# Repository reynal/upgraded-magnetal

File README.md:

# upgraded-magnetal
Add more controls, baby, add more controls (a MIDI/OSC controller with every control you can think of)

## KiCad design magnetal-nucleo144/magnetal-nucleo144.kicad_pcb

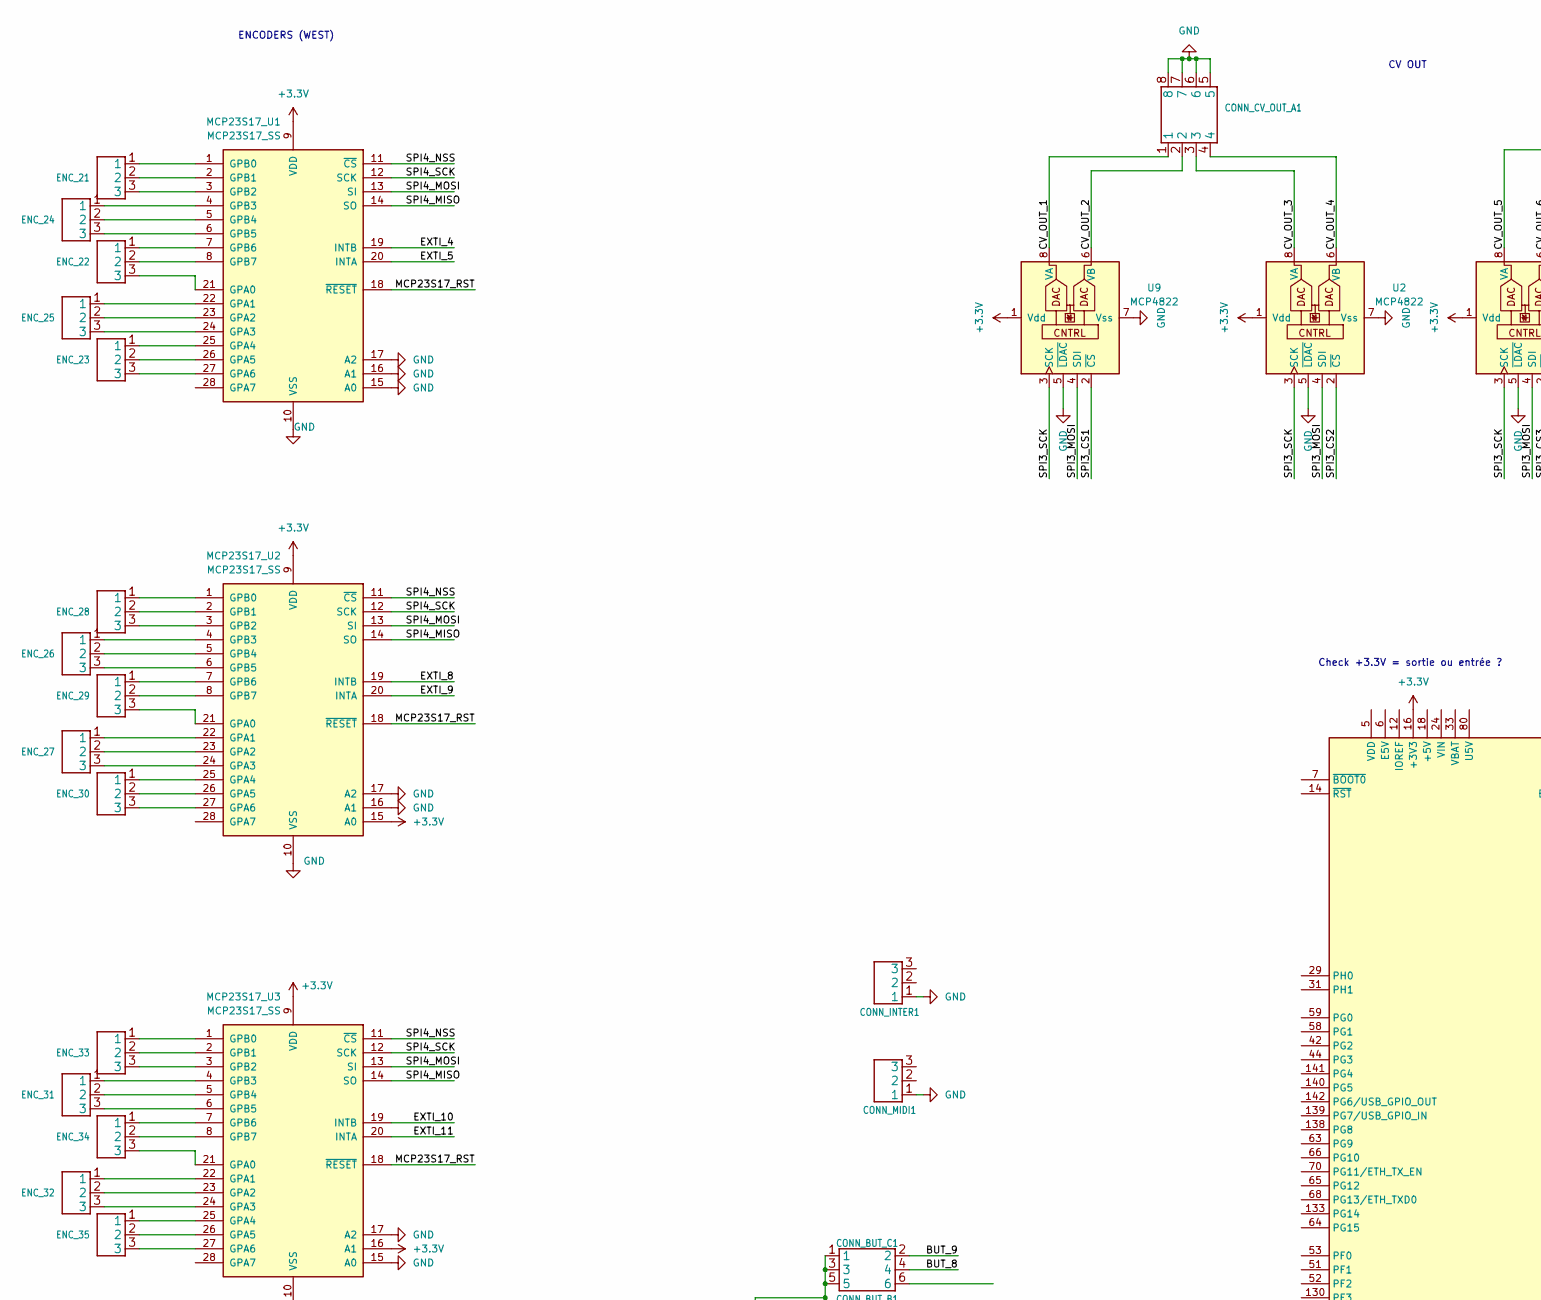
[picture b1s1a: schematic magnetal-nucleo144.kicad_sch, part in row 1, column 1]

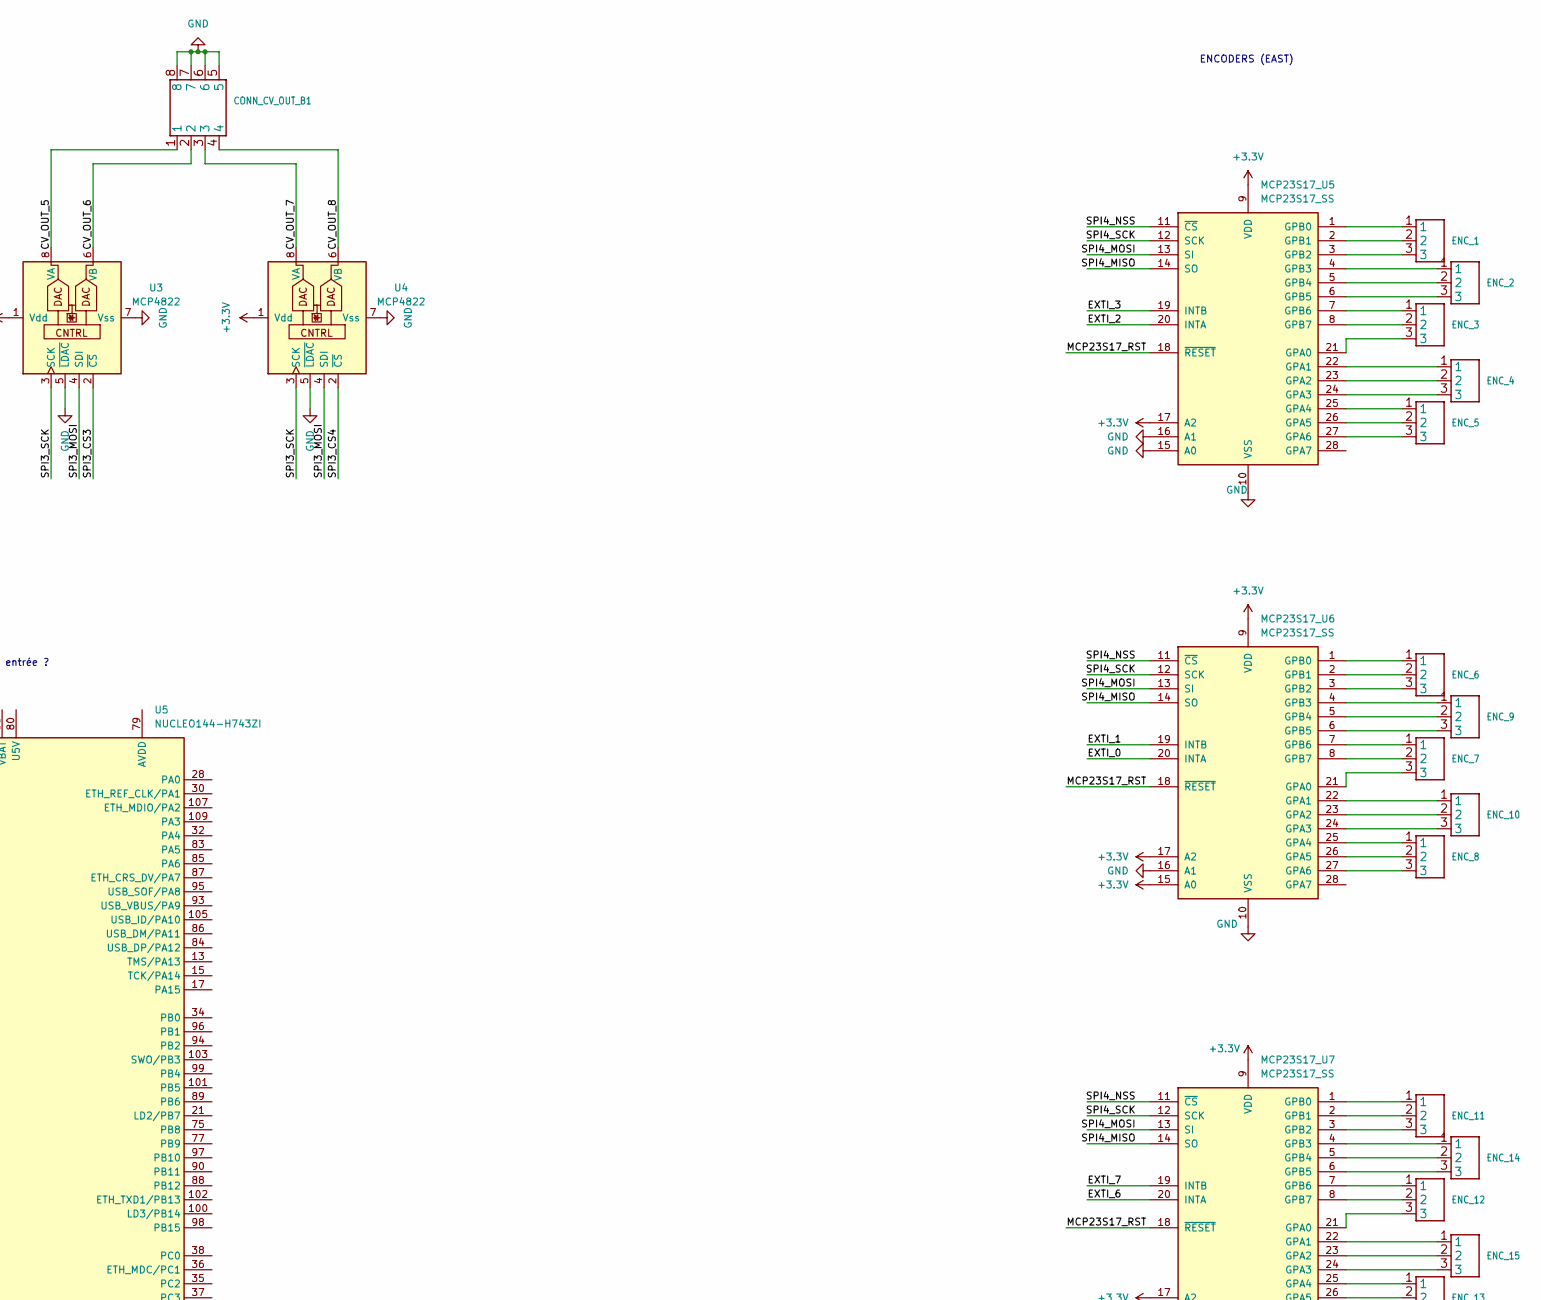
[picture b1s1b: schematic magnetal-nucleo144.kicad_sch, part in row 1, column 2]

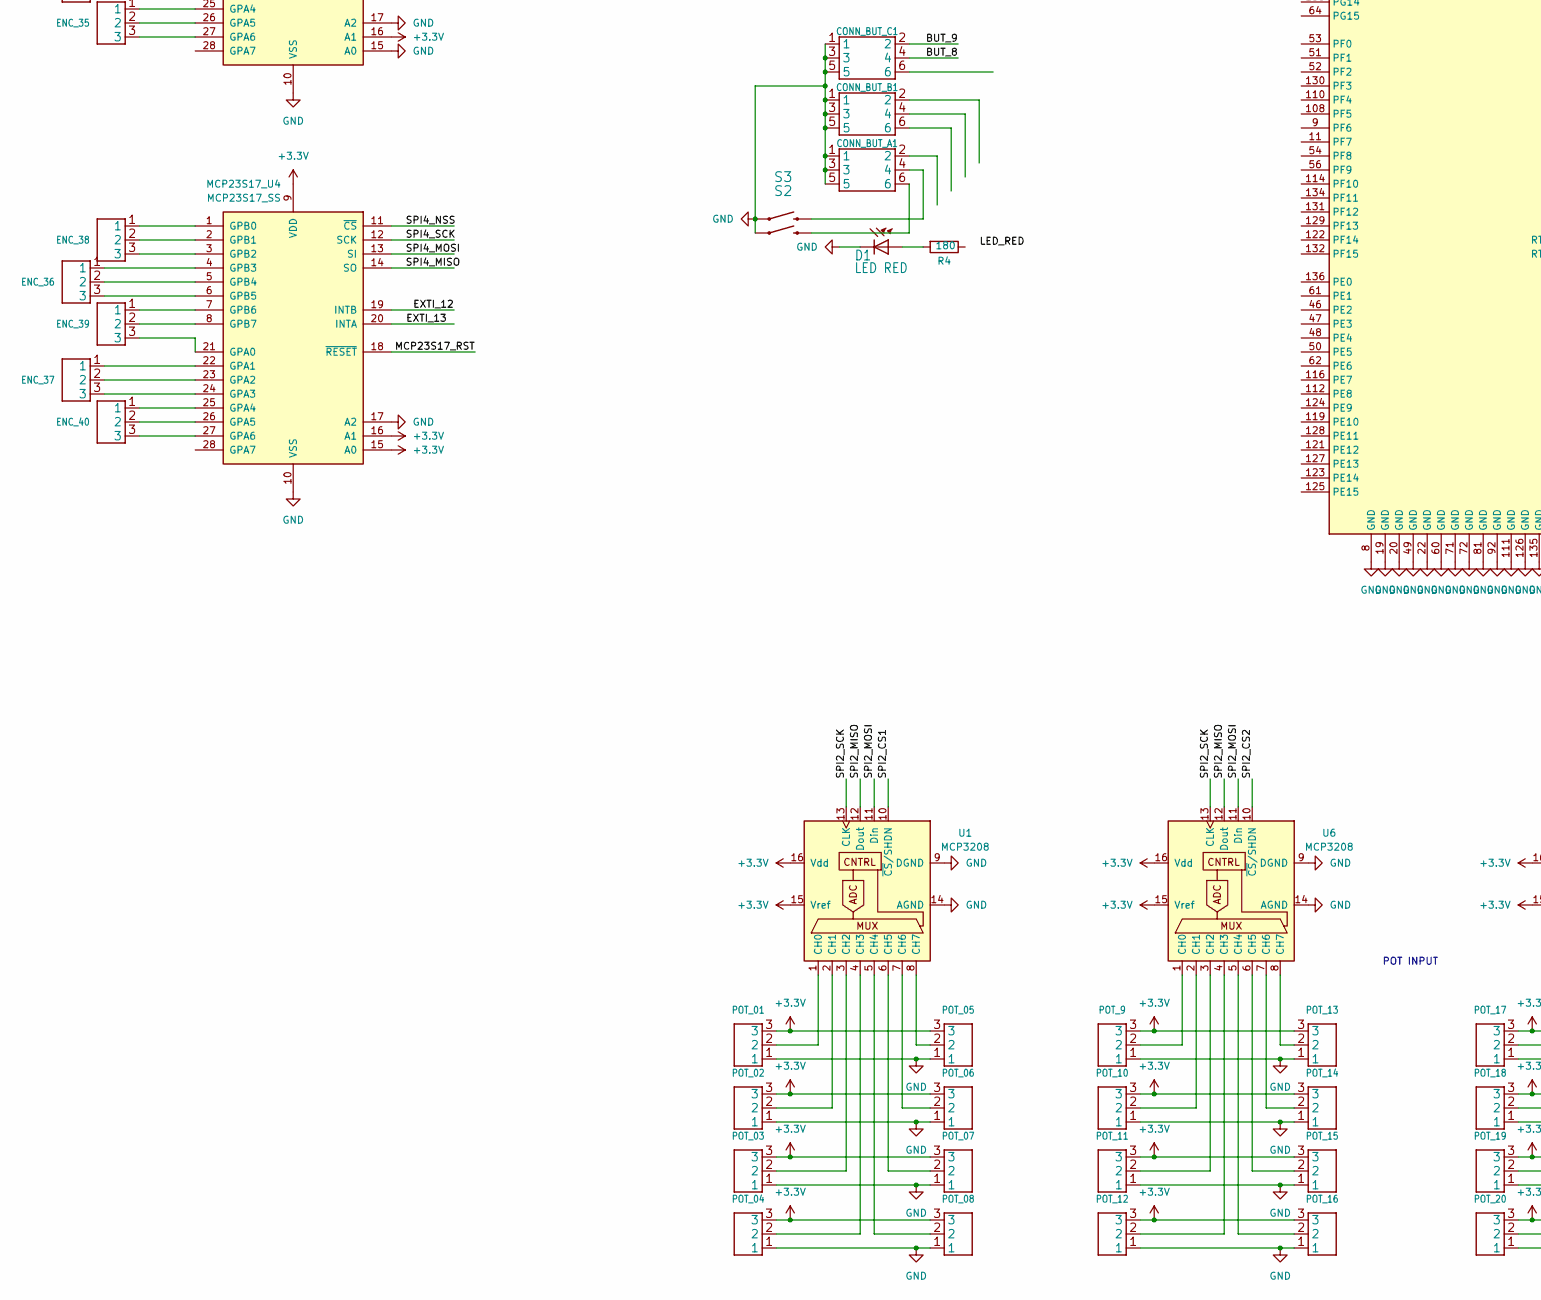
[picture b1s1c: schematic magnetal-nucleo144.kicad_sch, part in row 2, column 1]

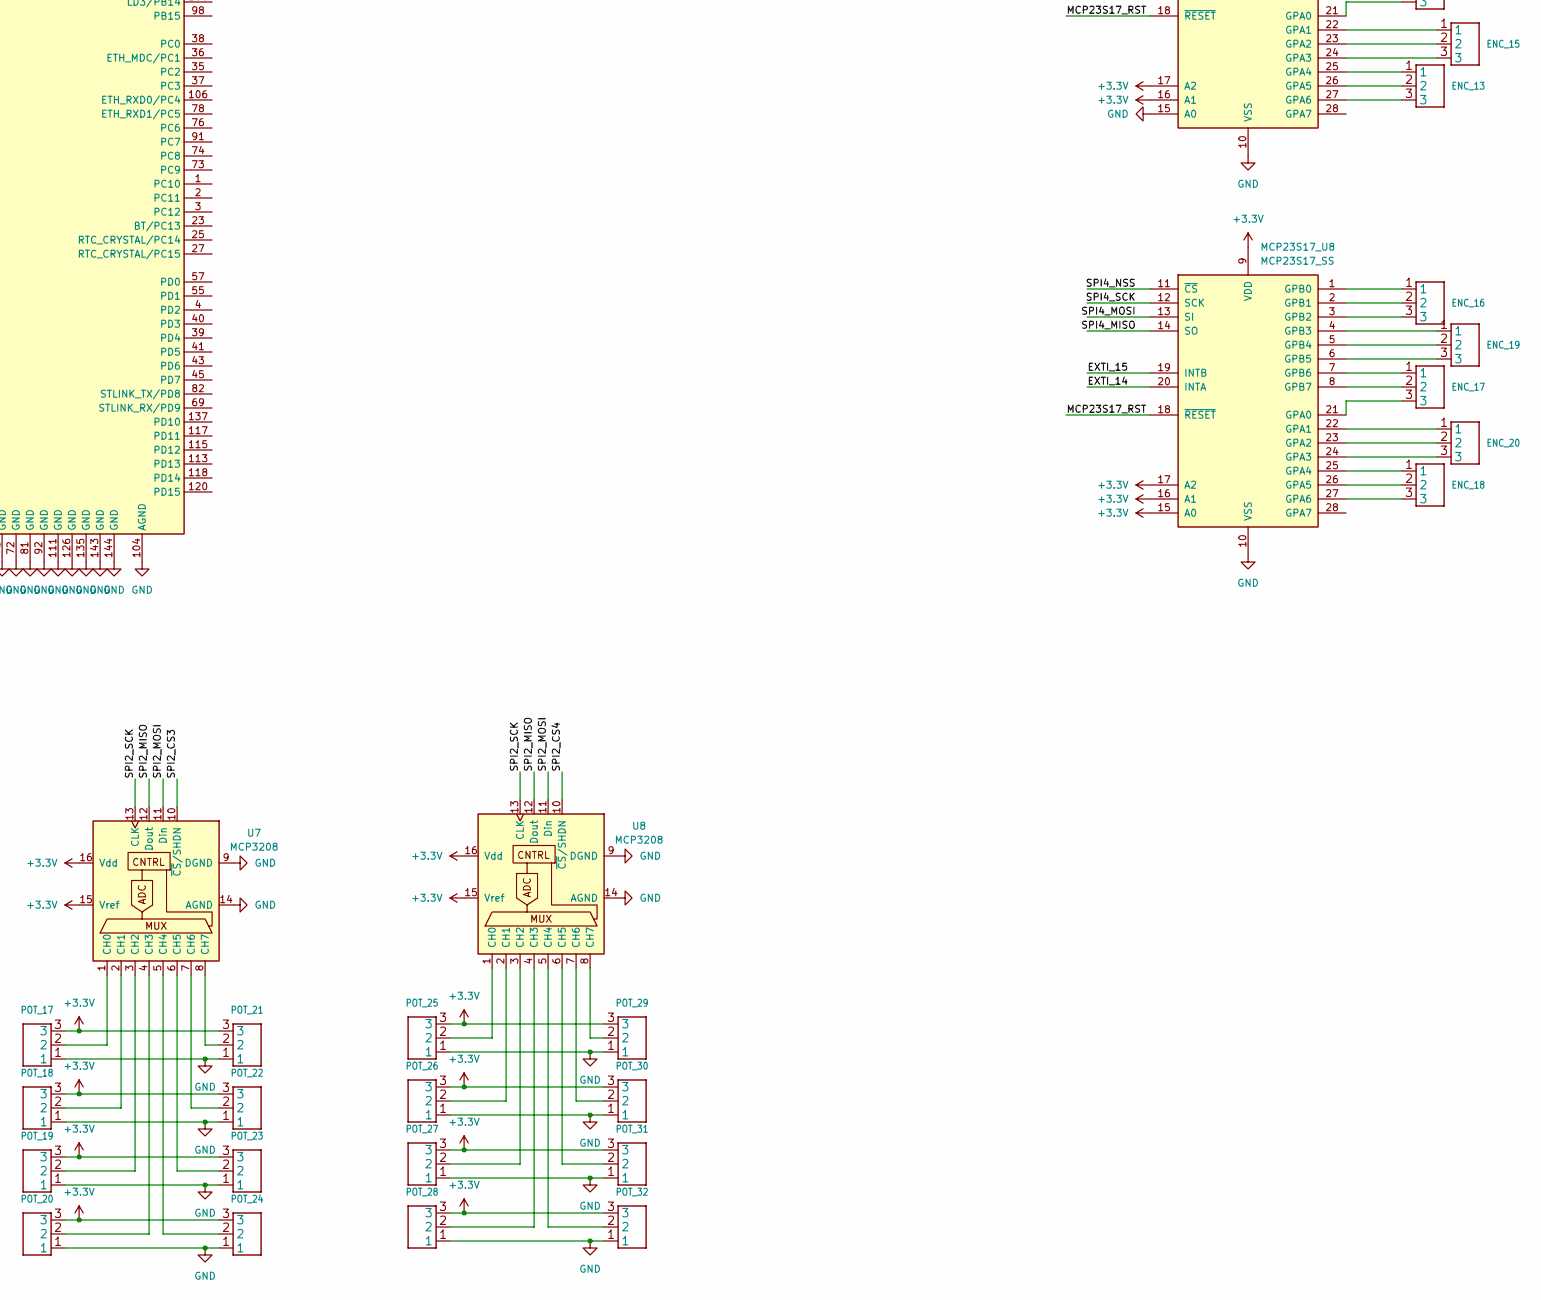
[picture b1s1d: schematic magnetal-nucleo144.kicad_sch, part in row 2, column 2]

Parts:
CONN_BUT_A1: M03X2
CONN_BUT_B1: M03X2
CONN_BUT_C1: M03X2
CONN_CV_OUT_A1: M04X2-FLOW_CONTROLER
CONN_CV_OUT_B1: M04X2-FLOW_CONTROLER
CONN_INTER1: M03
CONN_MIDI1: M03
D1: LED RED; 0805-LED
ENC_1, ENC_2, ENC_3, ENC_4, ENC_5, ENC_6, ENC_7, ENC_8, ENC_9, ENC_10, ENC_11, ENC_12, ENC_13, ENC_14, ENC_15, ENC_16, ENC_17, ENC_18, ENC_19, ENC_20, ENC_21, ENC_22, ENC_23, ENC_24, ENC_25, ENC_26, ENC_27, ENC_28, ENC_29, ENC_30, ENC_31, ENC_32, ENC_33, ENC_34, ENC_35, ENC_36, ENC_37, ENC_38, ENC_39, ENC_40: M03
MCP23S17_U1, MCP23S17_U2, MCP23S17_U3, MCP23S17_U4, MCP23S17_U5, MCP23S17_U6, MCP23S17_U7, MCP23S17_U8: MCP23S17_SS; SSOP-28_5.3x10.2mm_P0.65mm
POT_01, POT_02, POT_03, POT_04, POT_05, POT_06, POT_07, POT_08, POT_9, POT_10, POT_11, POT_12, POT_13, POT_14, POT_15, POT_16, POT_17, POT_18, POT_19, POT_20, POT_21, POT_22, POT_23, POT_24, POT_25, POT_26, POT_27, POT_28, POT_29, POT_30, POT_31, POT_32: M03
R4: 180; R_0805_2012Metric_Pad1.20x1.40mm_HandSolder
S2, S3: TACTILE_SWITCH_PTH_6.0MM_KIT
U1, U6, U7, U8: MCP3208; SOIC-16_3.9x9.9mm_P1.27mm
U2, U3, U4, U9: MCP4822; MSOP-8_3x3mm_P0.65mm
U5: NUCLEO144-H743ZI; ST_Morpho_Connector_144_STLink

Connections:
+3.3V: MCP23S17_U1.9 (VDD), MCP23S17_U2.9 (VDD), MCP23S17_U2.15 (A0), MCP23S17_U3.9 (VDD), MCP23S17_U3.16 (A1), MCP23S17_U4.9 (VDD), MCP23S17_U4.15 (A0), MCP23S17_U4.16 (A1), MCP23S17_U5.9 (VDD), MCP23S17_U5.17 (A2), MCP23S17_U6.9 (VDD), MCP23S17_U6.15 (A0), MCP23S17_U6.17 (A2), MCP23S17_U7.9 (VDD), MCP23S17_U7.16 (A1), MCP23S17_U7.17 (A2), MCP23S17_U8.9 (VDD), MCP23S17_U8.15 (A0), MCP23S17_U8.16 (A1), MCP23S17_U8.17 (A2), POT_01.3, POT_02.3, POT_03.3, POT_04.3, POT_05.3, POT_06.3, POT_07.3, POT_08.3, POT_9.3, POT_10.3, POT_11.3, POT_12.3, POT_13.3, POT_14.3, POT_15.3, POT_16.3, POT_17.3, POT_18.3, POT_19.3, POT_20.3, POT_21.3, POT_22.3, POT_23.3, POT_24.3, POT_25.3, POT_26.3, POT_27.3, POT_28.3, POT_29.3, POT_30.3, POT_31.3, POT_32.3, U1.15 (Vref), U1.16 (Vdd), U2.1 (Vdd), U3.1 (Vdd), U4.1 (Vdd), U5.16 (+3V3), U6.15 (Vref), U6.16 (Vdd), U7.15 (Vref), U7.16 (Vdd), U8.15 (Vref), U8.16 (Vdd), U9.1 (Vdd)
/BUT_8: CONN_BUT_C1.4
/BUT_9: CONN_BUT_C1.2
/CV_OUT_1: CONN_CV_OUT_A1.1, U9.8 (VA)
/CV_OUT_2: CONN_CV_OUT_A1.2, U9.6 (VB)
/CV_OUT_3: CONN_CV_OUT_A1.3, U2.8 (VA)
/CV_OUT_4: CONN_CV_OUT_A1.4, U2.6 (VB)
/CV_OUT_5: CONN_CV_OUT_B1.1, U3.8 (VA)
/CV_OUT_6: CONN_CV_OUT_B1.2, U3.6 (VB)
/CV_OUT_7: CONN_CV_OUT_B1.3, U4.8 (VA)
/CV_OUT_8: CONN_CV_OUT_B1.4, U4.6 (VB)
/EXTI_0: MCP23S17_U6.20 (INTA)
/EXTI_1: MCP23S17_U6.19 (INTB)
/EXTI_2: MCP23S17_U5.20 (INTA)
/EXTI_3: MCP23S17_U5.19 (INTB)
/EXTI_4: MCP23S17_U1.19 (INTB)
/EXTI_5: MCP23S17_U1.20 (INTA)
/EXTI_6: MCP23S17_U7.20 (INTA)
/EXTI_7: MCP23S17_U7.19 (INTB)
/EXTI_8: MCP23S17_U2.19 (INTB)
/EXTI_9: MCP23S17_U2.20 (INTA)
/EXTI_10: MCP23S17_U3.19 (INTB)
/EXTI_11: MCP23S17_U3.20 (INTA)
/EXTI_12: MCP23S17_U4.19 (INTB)
/EXTI_13: MCP23S17_U4.20 (INTA)
/EXTI_14: MCP23S17_U8.20 (INTA)
/EXTI_15: MCP23S17_U8.19 (INTB)
/MCP23S17_RST: MCP23S17_U1.18 (~RESET), MCP23S17_U2.18 (~RESET), MCP23S17_U3.18 (~RESET), MCP23S17_U4.18 (~RESET), MCP23S17_U5.18 (~RESET), MCP23S17_U6.18 (~RESET), MCP23S17_U7.18 (~RESET), MCP23S17_U8.18 (~RESET)
/SPI2_CS1: U1.10 (~CS/SHDN)
/SPI2_CS2: U6.10 (~CS/SHDN)
/SPI2_CS3: U7.10 (~CS/SHDN)
/SPI2_CS4: U8.10 (~CS/SHDN)
/SPI2_MISO: U1.12 (Dout), U6.12 (Dout), U7.12 (Dout), U8.12 (Dout)
/SPI2_MOSI: U1.11 (Din), U6.11 (Din), U7.11 (Din), U8.11 (Din)
/SPI2_SCK: U1.13 (CLK), U6.13 (CLK), U7.13 (CLK), U8.13 (CLK)
/SPI3_CS1: U9.2 (~CS)
/SPI3_CS2: U2.2 (~CS)
/SPI3_CS3: U3.2 (~CS)
/SPI3_CS4: U4.2 (~CS)
/SPI3_MOSI: U2.4 (SDI), U3.4 (SDI), U4.4 (SDI), U9.4 (SDI)
/SPI3_SCK: U2.3 (SCK), U3.3 (SCK), U4.3 (SCK), U9.3 (SCK)
/SPI4_MISO: MCP23S17_U1.14 (SO), MCP23S17_U2.14 (SO), MCP23S17_U3.14 (SO), MCP23S17_U4.14 (SO), MCP23S17_U5.14 (SO), MCP23S17_U6.14 (SO), MCP23S17_U7.14 (SO), MCP23S17_U8.14 (SO)
/SPI4_MOSI: MCP23S17_U1.13 (SI), MCP23S17_U2.13 (SI), MCP23S17_U3.13 (SI), MCP23S17_U4.13 (SI), MCP23S17_U5.13 (SI), MCP23S17_U6.13 (SI), MCP23S17_U7.13 (SI), MCP23S17_U8.13 (SI)
/SPI4_NSS: MCP23S17_U1.11 (~CS), MCP23S17_U2.11 (~CS), MCP23S17_U3.11 (~CS), MCP23S17_U4.11 (~CS), MCP23S17_U5.11 (~CS), MCP23S17_U6.11 (~CS), MCP23S17_U7.11 (~CS), MCP23S17_U8.11 (~CS)
/SPI4_SCK: MCP23S17_U1.12 (SCK), MCP23S17_U2.12 (SCK), MCP23S17_U3.12 (SCK), MCP23S17_U4.12 (SCK), MCP23S17_U5.12 (SCK), MCP23S17_U6.12 (SCK), MCP23S17_U7.12 (SCK), MCP23S17_U8.12 (SCK)
GND: CONN_BUT_A1.1, CONN_BUT_A1.3, CONN_BUT_A1.5, CONN_BUT_B1.1, CONN_BUT_B1.3, CONN_BUT_B1.5, CONN_BUT_C1.1, CONN_BUT_C1.3, CONN_BUT_C1.5, CONN_CV_OUT_A1.5, CONN_CV_OUT_A1.6, CONN_CV_OUT_A1.7, CONN_CV_OUT_A1.8, CONN_CV_OUT_B1.5, CONN_CV_OUT_B1.6, CONN_CV_OUT_B1.7, CONN_CV_OUT_B1.8, CONN_INTER1.1, CONN_MIDI1.1, D1.C, MCP23S17_U1.10 (VSS), MCP23S17_U1.15 (A0), MCP23S17_U1.16 (A1), MCP23S17_U1.17 (A2), MCP23S17_U2.10 (VSS), MCP23S17_U2.16 (A1), MCP23S17_U2.17 (A2), MCP23S17_U3.10 (VSS), MCP23S17_U3.15 (A0), MCP23S17_U3.17 (A2), MCP23S17_U4.10 (VSS), MCP23S17_U4.17 (A2), MCP23S17_U5.10 (VSS), MCP23S17_U5.15 (A0), MCP23S17_U5.16 (A1), MCP23S17_U6.10 (VSS), MCP23S17_U6.16 (A1), MCP23S17_U7.10 (VSS), MCP23S17_U7.15 (A0), MCP23S17_U8.10 (VSS), POT_01.1, POT_02.1, POT_03.1, POT_04.1, POT_05.1, POT_06.1, POT_07.1, POT_08.1, POT_9.1, POT_10.1, POT_11.1, POT_12.1, POT_13.1, POT_14.1, POT_15.1, POT_16.1, POT_17.1, POT_18.1, POT_19.1, POT_20.1, POT_21.1, POT_22.1, POT_23.1, POT_24.1, POT_25.1, POT_26.1, POT_27.1, POT_28.1, POT_29.1, POT_30.1, POT_31.1, POT_32.1, S2.1, S3.1, U1.9 (DGND), U1.14 (AGND), U2.5 (~LDAC), U2.7 (Vss), U3.5 (~LDAC), U3.7 (Vss), U4.5 (~LDAC), U4.7 (Vss), U5.8 (GND), U5.19 (GND), U5.20 (GND), U5.22 (GND), U5.49 (GND), U5.60 (GND), U5.71 (GND), U5.72 (GND), U5.81 (GND), U5.92 (GND), U5.104 (AGND), U5.111 (GND), U5.126 (GND), U5.135 (GND), U5.143 (GND), U5.144 (GND), U6.9 (DGND), U6.14 (AGND), U7.9 (DGND), U7.14 (AGND), U8.9 (DGND), U8.14 (AGND), U9.5 (~LDAC), U9.7 (Vss); also elsewhere on the board
unnamed: D1.A, R4.2
unnamed: ENC_22.3, MCP23S17_U1.21 (GPA0)
unnamed: ENC_25.1, MCP23S17_U1.22 (GPA1)
unnamed: ENC_25.2, MCP23S17_U1.23 (GPA2)
unnamed: ENC_25.3, MCP23S17_U1.24 (GPA3)
unnamed: ENC_23.1, MCP23S17_U1.25 (GPA4)
unnamed: ENC_23.2, MCP23S17_U1.26 (GPA5)
unnamed: ENC_23.3, MCP23S17_U1.27 (GPA6)
unnamed: ENC_21.1, MCP23S17_U1.1 (GPB0)
unnamed: ENC_21.2, MCP23S17_U1.2 (GPB1)
unnamed: ENC_21.3, MCP23S17_U1.3 (GPB2)
unnamed: ENC_24.1, MCP23S17_U1.4 (GPB3)
unnamed: ENC_24.2, MCP23S17_U1.5 (GPB4)
unnamed: ENC_24.3, MCP23S17_U1.6 (GPB5)
unnamed: ENC_22.1, MCP23S17_U1.7 (GPB6)
unnamed: ENC_22.2, MCP23S17_U1.8 (GPB7)
unnamed: ENC_29.3, MCP23S17_U2.21 (GPA0)
unnamed: ENC_27.1, MCP23S17_U2.22 (GPA1)
unnamed: ENC_27.2, MCP23S17_U2.23 (GPA2)
unnamed: ENC_27.3, MCP23S17_U2.24 (GPA3)
unnamed: ENC_30.1, MCP23S17_U2.25 (GPA4)
unnamed: ENC_30.2, MCP23S17_U2.26 (GPA5)
unnamed: ENC_30.3, MCP23S17_U2.27 (GPA6)
unnamed: ENC_28.1, MCP23S17_U2.1 (GPB0)
unnamed: ENC_28.2, MCP23S17_U2.2 (GPB1)
unnamed: ENC_28.3, MCP23S17_U2.3 (GPB2)
unnamed: ENC_26.1, MCP23S17_U2.4 (GPB3)
unnamed: ENC_26.2, MCP23S17_U2.5 (GPB4)
unnamed: ENC_26.3, MCP23S17_U2.6 (GPB5)
unnamed: ENC_29.1, MCP23S17_U2.7 (GPB6)
unnamed: ENC_29.2, MCP23S17_U2.8 (GPB7)
unnamed: ENC_34.3, MCP23S17_U3.21 (GPA0)
unnamed: ENC_32.1, MCP23S17_U3.22 (GPA1)
unnamed: ENC_32.2, MCP23S17_U3.23 (GPA2)
unnamed: ENC_32.3, MCP23S17_U3.24 (GPA3)
unnamed: ENC_35.1, MCP23S17_U3.25 (GPA4)
unnamed: ENC_35.2, MCP23S17_U3.26 (GPA5)
unnamed: ENC_35.3, MCP23S17_U3.27 (GPA6)
unnamed: ENC_33.1, MCP23S17_U3.1 (GPB0)
unnamed: ENC_33.2, MCP23S17_U3.2 (GPB1)
unnamed: ENC_33.3, MCP23S17_U3.3 (GPB2)
unnamed: ENC_31.1, MCP23S17_U3.4 (GPB3)
unnamed: ENC_31.2, MCP23S17_U3.5 (GPB4)
unnamed: ENC_31.3, MCP23S17_U3.6 (GPB5)
unnamed: ENC_34.1, MCP23S17_U3.7 (GPB6)
unnamed: ENC_34.2, MCP23S17_U3.8 (GPB7)
unnamed: ENC_39.3, MCP23S17_U4.21 (GPA0)
unnamed: ENC_37.1, MCP23S17_U4.22 (GPA1)
unnamed: ENC_37.2, MCP23S17_U4.23 (GPA2)
unnamed: ENC_37.3, MCP23S17_U4.24 (GPA3)
unnamed: ENC_40.1, MCP23S17_U4.25 (GPA4)
unnamed: ENC_40.2, MCP23S17_U4.26 (GPA5)
unnamed: ENC_40.3, MCP23S17_U4.27 (GPA6)
unnamed: ENC_38.1, MCP23S17_U4.1 (GPB0)
unnamed: ENC_38.2, MCP23S17_U4.2 (GPB1)
unnamed: ENC_38.3, MCP23S17_U4.3 (GPB2)
unnamed: ENC_36.1, MCP23S17_U4.4 (GPB3)
unnamed: ENC_36.2, MCP23S17_U4.5 (GPB4)
unnamed: ENC_36.3, MCP23S17_U4.6 (GPB5)
unnamed: ENC_39.1, MCP23S17_U4.7 (GPB6)
unnamed: ENC_39.2, MCP23S17_U4.8 (GPB7)
unnamed: ENC_3.3, MCP23S17_U5.21 (GPA0)
unnamed: ENC_4.1, MCP23S17_U5.22 (GPA1)
unnamed: ENC_4.2, MCP23S17_U5.23 (GPA2)
unnamed: ENC_4.3, MCP23S17_U5.24 (GPA3)
unnamed: ENC_5.1, MCP23S17_U5.25 (GPA4)
unnamed: ENC_5.2, MCP23S17_U5.26 (GPA5)
unnamed: ENC_5.3, MCP23S17_U5.27 (GPA6)
unnamed: ENC_1.1, MCP23S17_U5.1 (GPB0)
unnamed: ENC_1.2, MCP23S17_U5.2 (GPB1)
unnamed: ENC_1.3, MCP23S17_U5.3 (GPB2)
unnamed: ENC_2.1, MCP23S17_U5.4 (GPB3)
unnamed: ENC_2.2, MCP23S17_U5.5 (GPB4)
unnamed: ENC_2.3, MCP23S17_U5.6 (GPB5)
unnamed: ENC_3.1, MCP23S17_U5.7 (GPB6)
unnamed: ENC_3.2, MCP23S17_U5.8 (GPB7)
unnamed: ENC_7.3, MCP23S17_U6.21 (GPA0)
unnamed: ENC_10.1, MCP23S17_U6.22 (GPA1)
unnamed: ENC_10.2, MCP23S17_U6.23 (GPA2)
unnamed: ENC_10.3, MCP23S17_U6.24 (GPA3)
unnamed: ENC_8.1, MCP23S17_U6.25 (GPA4)
unnamed: ENC_8.2, MCP23S17_U6.26 (GPA5)
unnamed: ENC_8.3, MCP23S17_U6.27 (GPA6)
unnamed: ENC_6.1, MCP23S17_U6.1 (GPB0)
unnamed: ENC_6.2, MCP23S17_U6.2 (GPB1)
unnamed: ENC_6.3, MCP23S17_U6.3 (GPB2)
unnamed: ENC_9.1, MCP23S17_U6.4 (GPB3)
unnamed: ENC_9.2, MCP23S17_U6.5 (GPB4)
unnamed: ENC_9.3, MCP23S17_U6.6 (GPB5)
unnamed: ENC_7.1, MCP23S17_U6.7 (GPB6)
unnamed: ENC_7.2, MCP23S17_U6.8 (GPB7)
unnamed: ENC_12.3, MCP23S17_U7.21 (GPA0)
unnamed: ENC_15.1, MCP23S17_U7.22 (GPA1)
unnamed: ENC_15.2, MCP23S17_U7.23 (GPA2)
unnamed: ENC_15.3, MCP23S17_U7.24 (GPA3)
unnamed: ENC_13.1, MCP23S17_U7.25 (GPA4)
unnamed: ENC_13.2, MCP23S17_U7.26 (GPA5)
unnamed: ENC_13.3, MCP23S17_U7.27 (GPA6)
unnamed: ENC_11.1, MCP23S17_U7.1 (GPB0)
unnamed: ENC_11.2, MCP23S17_U7.2 (GPB1)
unnamed: ENC_11.3, MCP23S17_U7.3 (GPB2)
unnamed: ENC_14.1, MCP23S17_U7.4 (GPB3)
unnamed: ENC_14.2, MCP23S17_U7.5 (GPB4)
unnamed: ENC_14.3, MCP23S17_U7.6 (GPB5)
unnamed: ENC_12.1, MCP23S17_U7.7 (GPB6)
unnamed: ENC_12.2, MCP23S17_U7.8 (GPB7)
unnamed: ENC_17.3, MCP23S17_U8.21 (GPA0)
unnamed: ENC_20.1, MCP23S17_U8.22 (GPA1)
unnamed: ENC_20.2, MCP23S17_U8.23 (GPA2)
unnamed: ENC_20.3, MCP23S17_U8.24 (GPA3)
unnamed: ENC_18.1, MCP23S17_U8.25 (GPA4)
unnamed: ENC_18.2, MCP23S17_U8.26 (GPA5)
unnamed: ENC_18.3, MCP23S17_U8.27 (GPA6)
unnamed: ENC_16.1, MCP23S17_U8.1 (GPB0)
unnamed: ENC_16.2, MCP23S17_U8.2 (GPB1)
unnamed: ENC_16.3, MCP23S17_U8.3 (GPB2)
unnamed: ENC_19.1, MCP23S17_U8.4 (GPB3)
unnamed: ENC_19.2, MCP23S17_U8.5 (GPB4)
unnamed: ENC_19.3, MCP23S17_U8.6 (GPB5)
unnamed: ENC_17.1, MCP23S17_U8.7 (GPB6)
unnamed: ENC_17.2, MCP23S17_U8.8 (GPB7)
unnamed: CONN_BUT_A1.6, S2.3 (2)
unnamed: CONN_BUT_A1.4, S3.3 (2)
unnamed: POT_01.2, U1.1 (CH0)
unnamed: POT_02.2, U1.2 (CH1)
unnamed: POT_03.2, U1.3 (CH2)
unnamed: POT_04.2, U1.4 (CH3)
unnamed: POT_08.2, U1.5 (CH4)
unnamed: POT_07.2, U1.6 (CH5)
unnamed: POT_06.2, U1.7 (CH6)
unnamed: POT_05.2, U1.8 (CH7)
unnamed: POT_9.2, U6.1 (CH0)
unnamed: POT_10.2, U6.2 (CH1)
unnamed: POT_11.2, U6.3 (CH2)
unnamed: POT_12.2, U6.4 (CH3)
unnamed: POT_16.2, U6.5 (CH4)
unnamed: POT_15.2, U6.6 (CH5)
unnamed: POT_14.2, U6.7 (CH6)
unnamed: POT_13.2, U6.8 (CH7)
unnamed: POT_17.2, U7.1 (CH0)
unnamed: POT_18.2, U7.2 (CH1)
unnamed: POT_19.2, U7.3 (CH2)
unnamed: POT_20.2, U7.4 (CH3)
unnamed: POT_24.2, U7.5 (CH4)
unnamed: POT_23.2, U7.6 (CH5)
unnamed: POT_22.2, U7.7 (CH6)
unnamed: POT_21.2, U7.8 (CH7)
unnamed: POT_25.2, U8.1 (CH0)
unnamed: POT_26.2, U8.2 (CH1)
unnamed: POT_27.2, U8.3 (CH2)
unnamed: POT_28.2, U8.4 (CH3)
unnamed: POT_32.2, U8.5 (CH4)
unnamed: POT_31.2, U8.6 (CH5)
unnamed: POT_30.2, U8.7 (CH6)
unnamed: POT_29.2, U8.8 (CH7)

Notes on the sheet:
Check +3.3V = sortie ou entrée ?
ENCODERS (WEST)
CV OUT
ENCODERS (EAST)
POT INPUT

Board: 2 copper layers, 104 parts (0 on the bottom side), 177 nets, no tracks yet.

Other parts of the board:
D2: LED_BLUE; 0805-LED
D3: LED GREEN; 0805-LED
R5, R6: 180; R_0805_2012Metric_Pad1.20x1.40mm_HandSolder
STM32H7: Nucleo; NUCLEO_BRD144

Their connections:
GND: D2.C, D3.C; also elsewhere on the board
unnamed: D2.A, R5.2
unnamed: D3.A, R6.2

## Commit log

2026-02-28 Initial commit. Kicad files + STM32MXCube config file (unfinished)
